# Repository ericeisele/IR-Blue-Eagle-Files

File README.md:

IR-Blue-Eagle-Files
===================

IR-Blue Thermal Imaging Smartphone Accessory
<p>
This fork of the IR Blue hardware design (originally by RHWorkshop) will miniaturize the smartphone accessory, while adding the following features:
<ul>
<li>-Rechargable 180mAh Li-poly battery</li>
<li>-Micro USB charging port</li>
<li>-Built in charge management and low battery disconnect to prevent deep discharge of the battery</li>
<li>-Highly efficient (>90%) voltage regulation for enhanced battery life</li>
<li>-All SMT assembly</li>
<li>-3D printable enclosures that snap onto iPhone 5</li>
<li>-3D templates to customize enclosure for specific phone models</li>
</ul>

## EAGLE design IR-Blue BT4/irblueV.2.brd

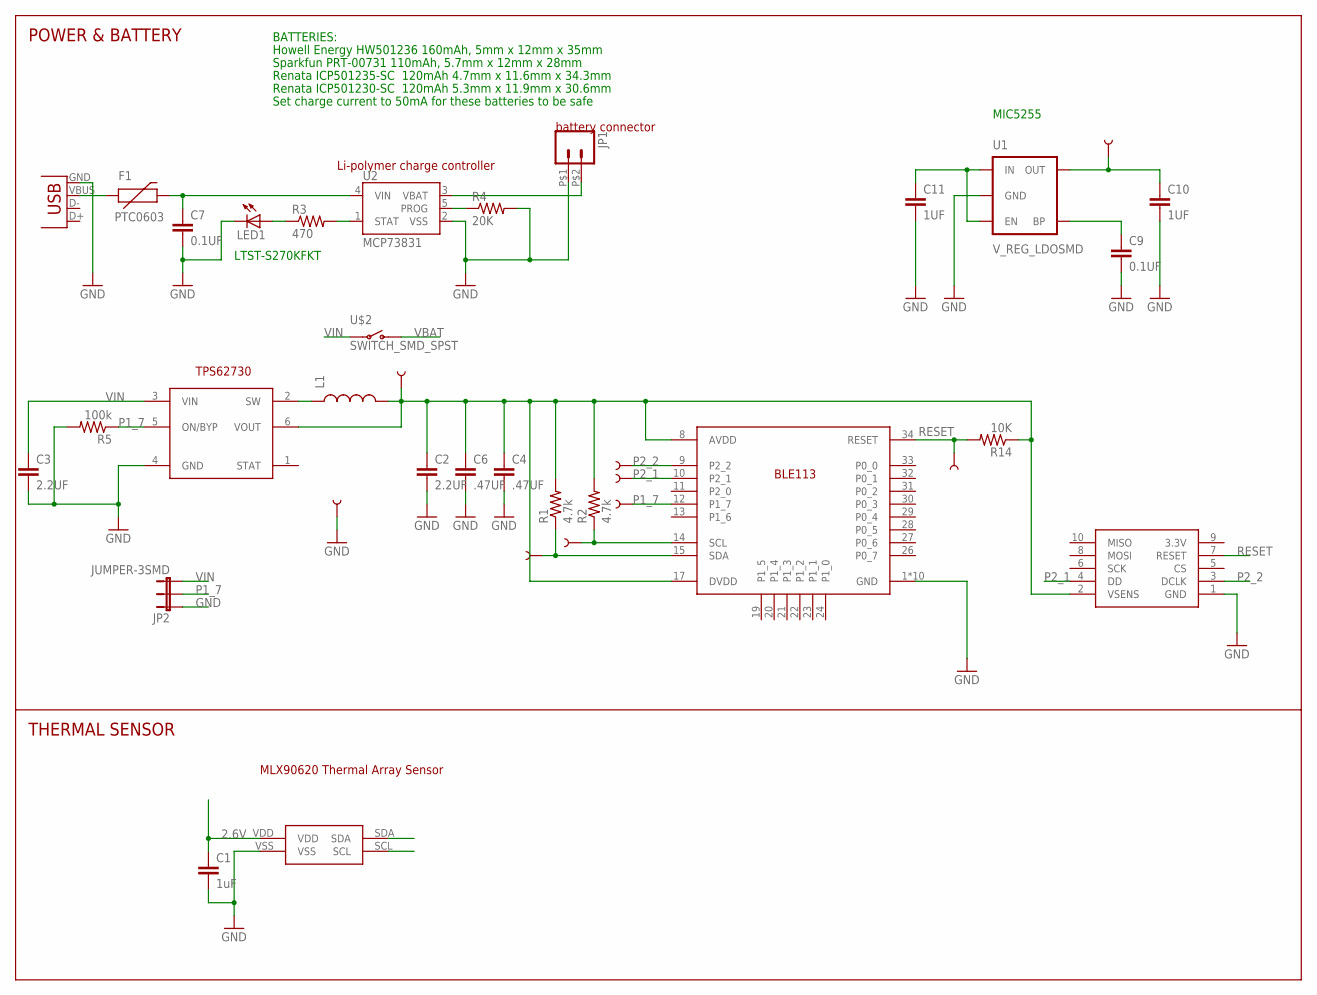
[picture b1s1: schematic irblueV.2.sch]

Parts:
C1: 1uF; 0402-CAP
C2, C3: 2.2UF; 0603-CAP
C4, C6: .47UF; 0402-CAP
C7, C9: 0.1UF; 0402-CAP
C10, C11: 1UF; 0402-CAP
F1: PTC0603; 0603
JP1: M02WIRE; 1X02_1-WIRE
JP2: JUMPER-3SMD; SJ_3
L1: INDUCTOR0805; 0805
LED1: LED0603; LED-0603
R1, R2: 4.7k; 0402-RES
R3: 470; 0402-RES
R4: 20K; 0402-RES
R5: 100k; 0402-RES
R14: 10K; 0402-RES
S1: MLX90620
TP1, TP2, TP3, TP4, TP5, TP6, TP7, TP8, TP9: TEST-POINT3X5; PAD.03X.05
U1: V_REG_LDOSMD; SOT23-5
U2: MCP73831; SOT23-5
U$1: TPS62730; SON-6
U$2: SWITCH_SMD_SPST; SWITCH-SPDT-SMD
U$5: BLE113
U$8: TAG_CONNECT_CC_DEBUGGER; TC2030-MCP-NL
X1: USB-MICROB

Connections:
2.6V: C1.1, C10.1, S1.VDD, TP9.P$1, U1.5 (OUT)
GND: C1.2, C2.2, C3.2, C4.2, C6.2, C7.2, C9.2, C10.2, C11.2, JP1.P$1 (1), JP2.1, LED1.C, R4.2, R5.2, S1.VSS, TP8.P$1, U1.2 (GND), U2.2 (VSS), U$1.4 (GND), U$5.1 (GND), U$5.2 (GND), U$5.3 (GND), U$5.4 (GND), U$5.5 (GND), U$5.6 (GND), U$5.7 (GND), U$5.18 (GND), U$5.25 (GND), U$5.36 (GND), U$8.1 (GND), X1.GND
unnamed: F1.1, X1.VBUS
unnamed: L1.1, U$1.2 (SW)
unnamed: R4.1, U2.5 (PROG)
unnamed: C7.1, F1.2, U2.4 (VIN)
unnamed: R3.2, U2.1 (STAT)
unnamed: LED1.A, R3.1
unnamed: C9.1, U1.4 (BP)
P1_7: JP2.2, R5.1, TP3.P$1, U$1.5 (ON/BYP), U$5.12 (P1_7)
P2_1: TP2.P$1, U$5.10 (P2_1), U$8.4 (DD)
P2_2: TP1.P$1, U$5.9 (P2_2), U$8.3 (DCLK)
RESET: R14.2, TP4.P$1, U$5.34 (RESET), U$8.7 (RESET)
SCL: R2.1, S1.SCL, TP5.P$1, U$5.14 (SCL)
SDA: R1.1, S1.SDA, TP6.P$1, U$5.15 (SDA)
VBAT: JP1.P$2 (2), U2.3 (VBAT), U$2.1 (O)
VIN: C3.1, C11.1, JP2.3, U1.1 (IN), U1.3 (EN), U$1.3 (VIN), U$2.2
VREG: C2.1, C4.1, C6.1, L1.2, R1.2, R2.2, R14.1, TP7.P$1, U$1.6 (VOUT), U$5.8 (AVDD), U$5.17 (DVDD), U$8.2 (VSENS)

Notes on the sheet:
BATTERIES:
Howell Energy HW501236 160mAh, 5mm x 12mm x 35mm
Sparkfun PRT-00731 110mAh, 5.7mm x 12mm x 28mm
Renata ICP501230-SC 120mAh 5.3mm x 11.9mm x 30.6mm
POWER & BATTERY
THERMAL SENSOR
Li-polymer charge controller
battery connector
MLX90620 Thermal Array Sensor
Renata ICP501235-SC 120mAh 4.7mm x 11.6mm x 34.3mm
Set charge current to 50mA for these batteries to be safe
LTST-S270KFKT
MIC5255

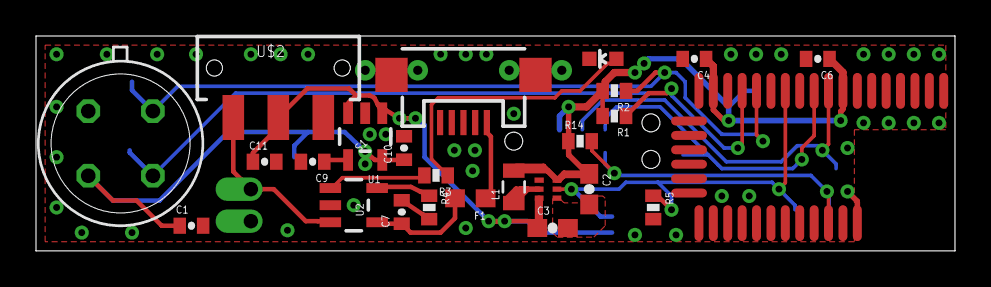
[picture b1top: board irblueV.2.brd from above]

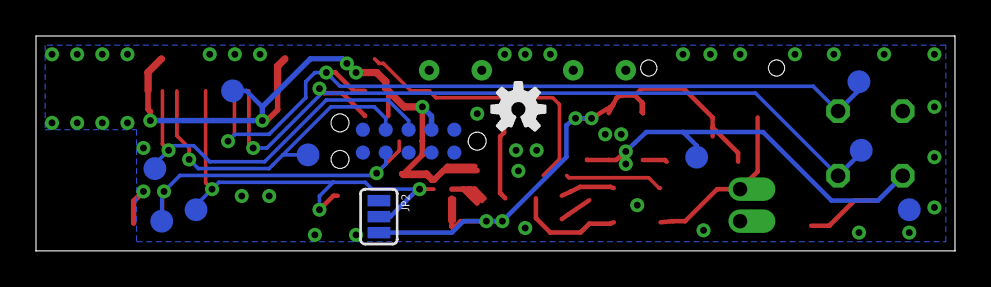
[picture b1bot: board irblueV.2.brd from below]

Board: 2 copper layers, 51.1 x 11.9 mm, 38 parts (12 on the bottom side), 18 nets.

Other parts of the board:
U$4: OSHW-LOGO-S

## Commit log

2013-10-16 Added new MLX90620 Eagle library
2014-01-12 Initial commit of redesigned IRBlue
    Redesigned the IRBlue smartphone thermal imaging accessory to include
    the new Texas Instruments CC2541 low energy Bluetooth chip, battery
    charging, efficient stepdown conversion with the TI TPS62730, and a 3D
    printed enclosure
2014-01-12 Cleaned up old files

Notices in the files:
parts and their libraries:
10.SparkFun: Licensing: CC v3.0 Share-Alike You are welcome to use this library for commercial purposes.
11.ee_projects: ©2009 ROFA.cz
